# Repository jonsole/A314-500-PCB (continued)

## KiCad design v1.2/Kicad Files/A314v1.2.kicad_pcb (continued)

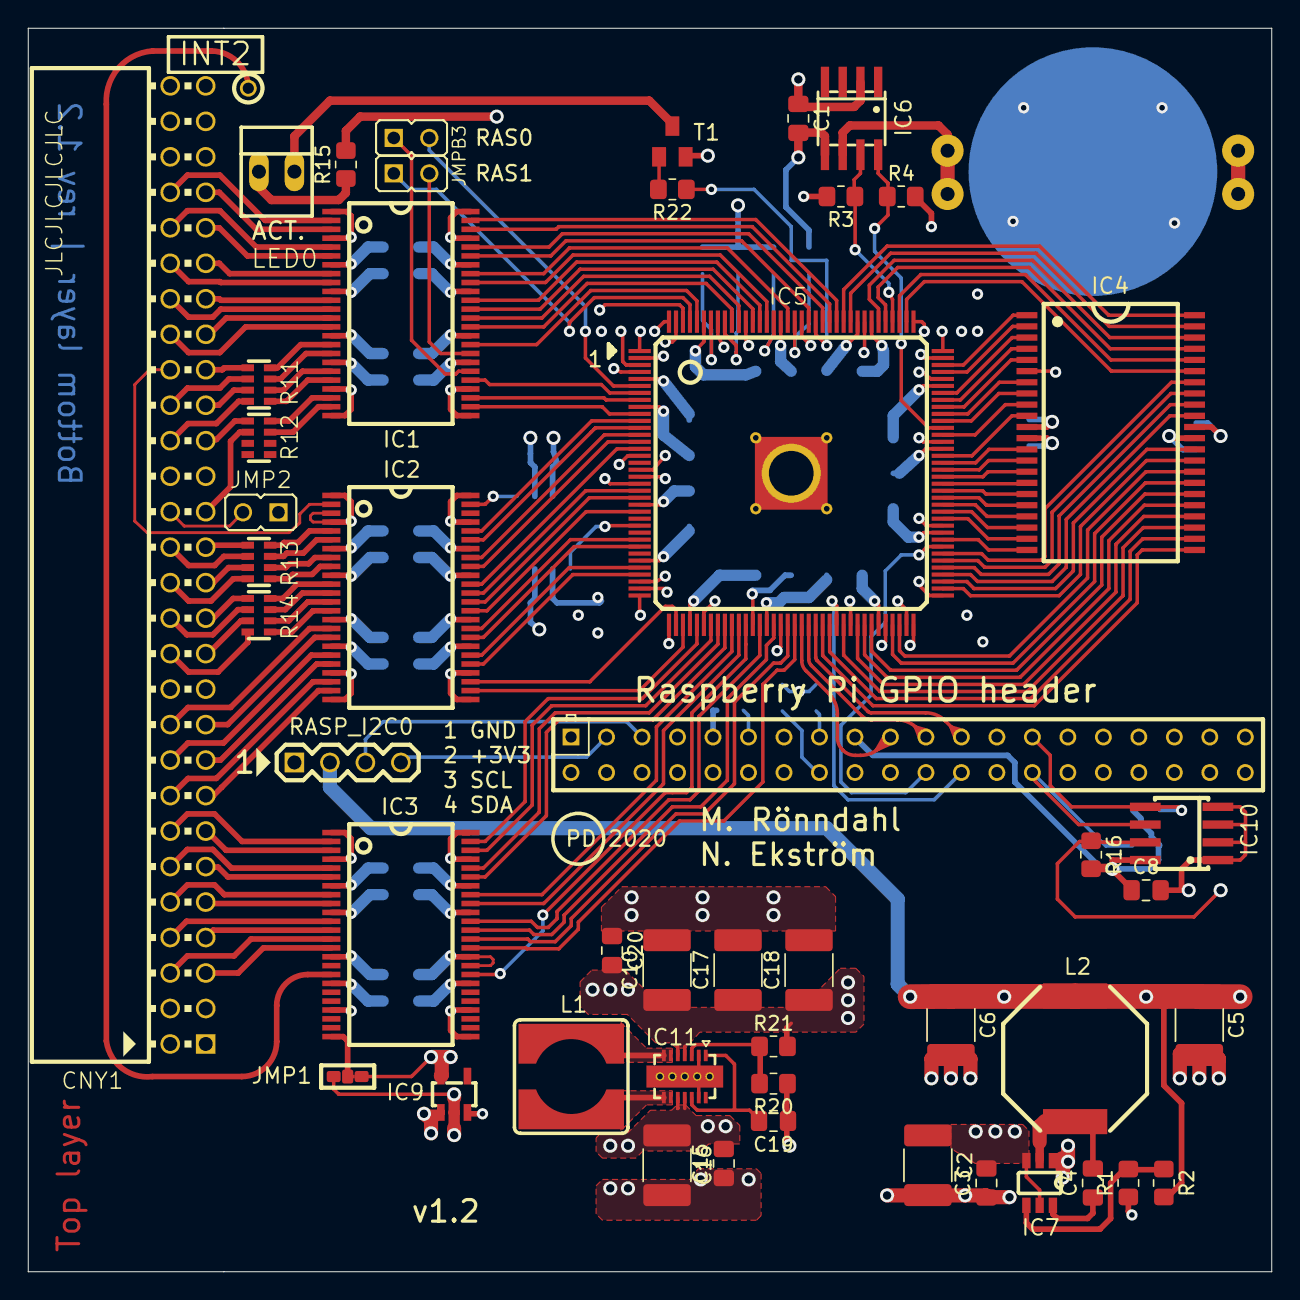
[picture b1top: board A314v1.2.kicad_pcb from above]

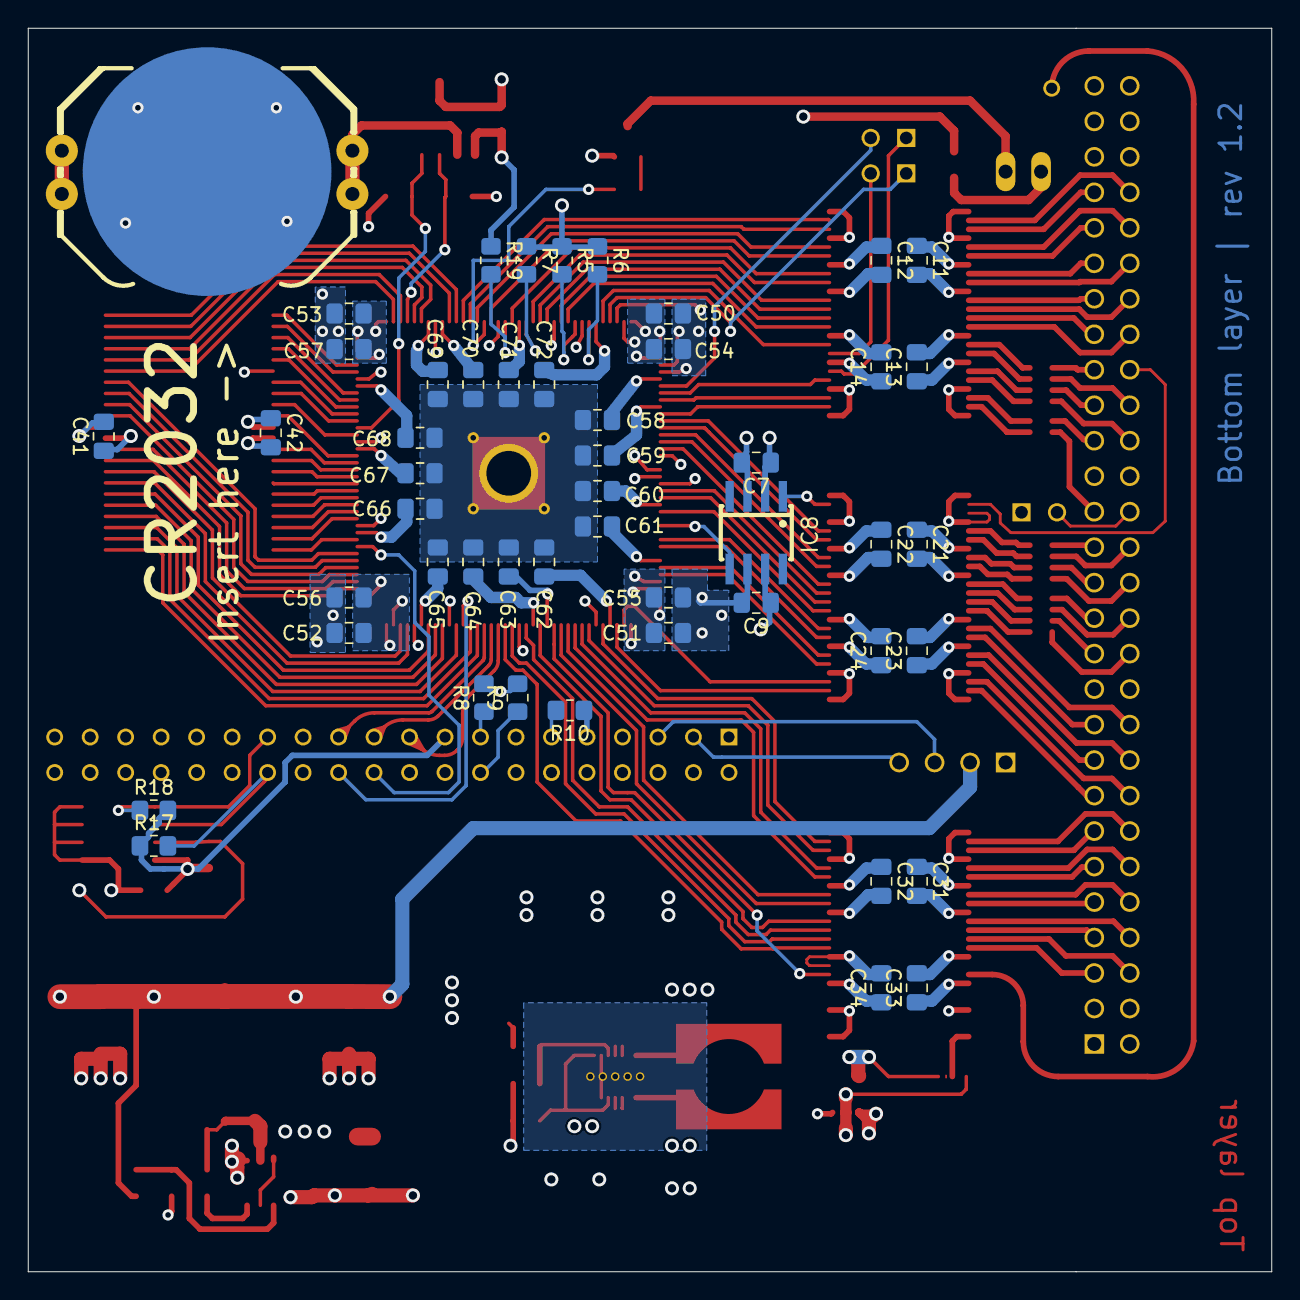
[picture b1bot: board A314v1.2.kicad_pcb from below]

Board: 4 copper layers, 89.0 x 89.0 mm, 99 parts (51 on the bottom side), 179 nets.

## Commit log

2026-03-16 Kicad Import
    PCB and Schematic imported into Kicad and ERC passing
2026-03-16 More cleanup
